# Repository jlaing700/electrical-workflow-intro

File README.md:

Note: There are two methods in which you can publish your work through Github. 
1. Using Git Bash CD (Command Prompts)
2. Using GitHub Desktop app and/or GitHub website.

Pick whichever you're comfortable with. If you're not a coding person, I recommend using method 2. 

Make sure you have created a GitHub account before you start and have it shared with one of the electrical to be added to Mechatronics GitHub organization. 

# 1. GitHub-Work-Flow-Intro-Project using Git Bash
Add a .txt file telling club members about you and what your goals are for Fall 2022 semester

## How to Contribute to the Repository
Here is a brief explanation on how to contribute to git and github

#### Git vs. Github
Git is a repository version control that is local to your computer only. This means only the user of the local computer has access to these files. It keeps track of any changes that are commited to it so that each iteration of a repo can be accessed. Be sure to update this each time you finish your work session for the day as it will act as a backup storage. Git is important for version control but also because this is where github will be pulling the files from whenever a "push" occurs. **You will need to install git onto your computer**

https://git-scm.com/downloads

Github is a cloud based repository viewer that allows a repository to be accessed via webapp. Github will act as a central location for all our individual tasks and develepments to be accessed from any computer connected to the internet. Changes should be comitted to Git first and then pushed to Github so anybody can access pull the changes to the repository.

#### Cloning
To make the initial link of a github repository onto your git, you must clone it. Here are the steps to doing so

1. Open git bash or linux terminal in the working directory of where you wish to store the repository files on your computer. This is can be done by right-clicking inside the folder you save the files and selecting "Git Bash Here"

2. Use the clone command to clone the github repository onto your git. It will automatically create a folder with the name of the repository with all of its contents
```
git clone https://github.com/Mechatronics-SDSU/electrical-workflow-intro.git
```

#### Branching
Every repository, in our case **GitHub_Work_Flow_Intro_Project**, has a **main** branch where the most up-to-date ready to ship version is held. This is to ensure there is always a deployable version at any point in the development and maintenance cycle. When new features or additions are being developed, typically a new branch is created with the name of that feature. This allows for a new location that new code, PCB designs, and updates can be saved without affecting the **main** branch. In our case, there currently exists a branch for each seperate piece to the project. Once one of the features/branches has been thoroughly tested and is stable, that branch is merged into the **main** branch. What this will do is copy all files from the initial development branch and merge them into the **main** branch so it becomes the most up-to-date version with these new features.

Here is an example of how to create a new branch off of main. Please use the following naming format for the branch **[Your_Full_Name]_[Description of Branch]**, for the intro project please use **dev** as your branch description.

#### Creating a New Branch Example

Create a new branch off of **electrical-workflow-intro** called "Tristan_dev"

```
git checkout -b Tristan_dev main
```

#### Git Workflow

Here is a step by step explanation of how a typical worksession goes

1. Open git bash or linux terminal in the working directory of where you store the repository files on your computer. This is can be done by right-clicking inside the folder you save the files and selecting "Git Bash Here"

2. Pull any and all changes from the github repository **main** to be saved into your local git. Note you must enter the exact branches you wish to update your local version of to the github version. See step 3 on how to change current branch. 
```
git pull
```

3. Enter the exact branch you wish to do development in. Important to do this step as failure to do so may result in conflicts
```
git checkout [Name_of_Branch]
```

4. Start developing as you normally do until you are all finished

5. Add the specific files that were worked on
```
git add file.txt

or

git add -A
```

6. Commit the changes to the added files to the local git with a message of what was changed. It is important to add a message as the commit will open up VIM expecting you to write a message in. **To avoid this issue, be sure to write the message in the initial commit command**
```
git commit -m "Programmed the Arduino to blink an LED every 5 seconds"
```

7. Push these commits in your local git to the github so everyone can pull these changes to their local computers
```
git push origin [Name_of_Branch]
```

8. A pop window will appear prompting for you github login information. Enter you username into the first window and click submit, then enter you password into the second window and click submit.
-----------------------------------------------------------------------------------------------------------------------------------------------------------------------

# 2. GitHub-Work-Flow-Intro-Project Using GitHub Desktop
**Download and install GitHub Desktop App on your computer: https://desktop.github.com/**

**Make sure you're using the same account for both GitHub website and GitHub Desktop App.**

## There are a total of 3 steps on how to contribute to the repository:
1. Cloning
2. Branching
3. Pushing 
-----------------------------------------------------------------------------------------------------------------------------------------------------------------------
- Cloning and Branching are usually only done once. 

- To contribute to a Repository, you must clone it on your local computer. 

- Branching is a cloned version of a repository in order to push any work you've done pertaining the intruction of that Repository. 

- Pushing is uploading your files/work you've done to GitHub where anyone who has access to the Repository can see your files that you pushed. 

In these steps below, l'll walk you through how to contribute to a Repository using GitHub Desktop app and GitHub website. 

-----------------------------------------------------------------------------------------------------------------------------------------------------------------------

1. Create a text file on your desktop. Within the text file, tell us about you and what your goals are for Fall 2022 semester. For more brownie points, add in any particular interests that you would like to work with/learn more about in our electrical team. 

Now that your text file is ready to be shared on GitHub, we'll first have to add yourself to this repository to create a branch. 

A branch is a cloned version of a repository. In this case, we'll create a branch named after your name (e.g: Fadi_dev) of this repository.

Within this new branch that you will create, you will be able to add in any files that pertains to the repository instructions. 

(More information about GitHub, Branching, and Cloning can be found in the sections above in method 1)

2. To add yourself to the repository, navigate and press the main branch on the GitHub website. 
Navigate to "Code" --> "Open with GitHub Desktop". From there, GitHub desktop will clone the repository of main branch and add it to your local computer. After the clone has finished, you will now be able to create your own personal branch. 
3. On the GitHub Desktop app, navigate to "Current branch" and press "New branch". Create a branch named after your name (e.g: Fadi_dev). 
You can also do this on the main GitHub website to create a branch. 

Congratualtions, you now have your own personal branch of this repository. 

4. After you have made your branch, navigate to it and press, you will notice that the README.md instructions are cloned to your branch. 
Next step is to add your .txt file that you have already made on your desktop. All thats left to do is to upload your .txt file to github **while** you're in your created branch (this is important). 

Once you've uploaded your text file, you should be able to see what you've wrote down on GitHub. Anyone who has access to this repository is also able to see it. 

-----------------------------------------------------------------------------------------------------------------------------------------------------------------------
**If you have any questions, reach out to Ken or sudo apt install better grades on Discord**

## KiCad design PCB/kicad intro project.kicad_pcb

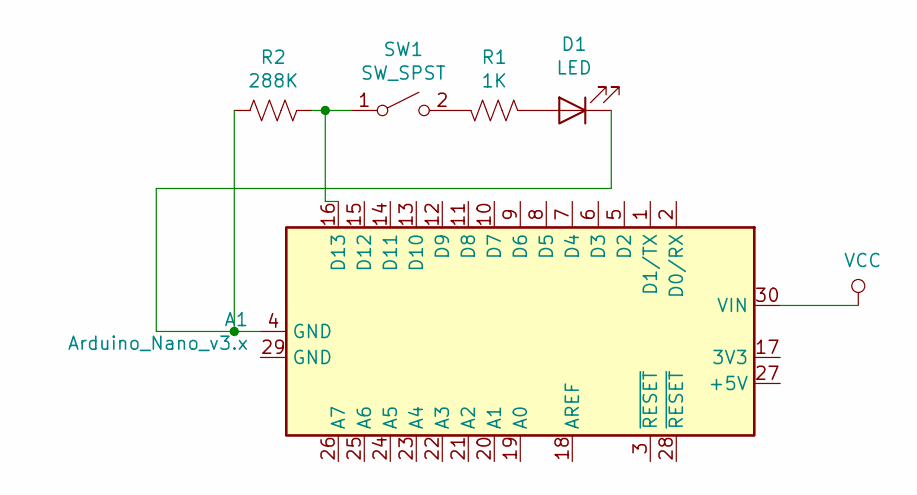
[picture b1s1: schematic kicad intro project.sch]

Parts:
A1: Arduino_Nano_v3.x; Arduino_Nano
D1: LED; LED_D3.0mm_Horizontal_O3.81mm_Z10.0mm
R1: 1K; R_Axial_DIN0204_L3.6mm_D1.6mm_P1.90mm_Vertical
R2: 288K; R_Axial_DIN0204_L3.6mm_D1.6mm_P1.90mm_Vertical
SW1: SW_SPST; TerminalBlock_RND_205-00012_1x02_P5.00mm_Horizontal

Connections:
unnamed: A1.4 (GND), D1.1 (K), R2.1
unnamed: A1.16 (D13), R2.2, SW1.1 (A)
unnamed: D1.2 (A), R1.2
unnamed: R1.1, SW1.2 (B)
VCC: A1.30 (VIN)

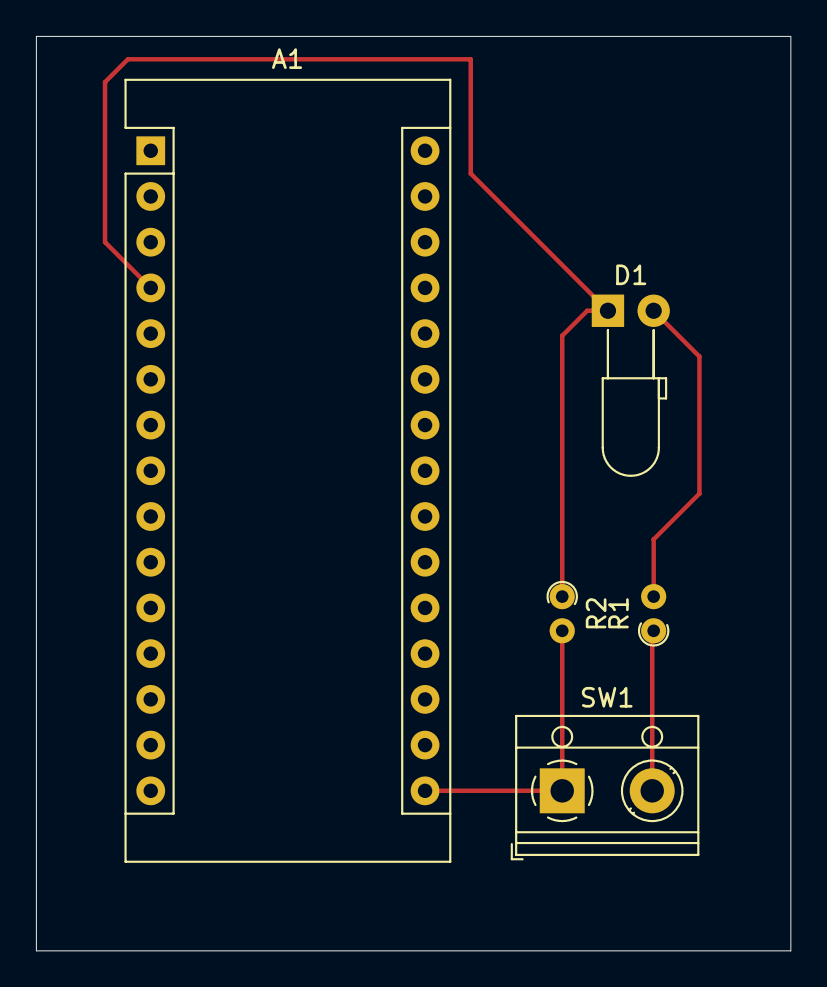
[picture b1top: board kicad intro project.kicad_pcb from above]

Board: 2 copper layers, 41.9 x 50.8 mm, 5 parts (0 on the bottom side), 4 nets.

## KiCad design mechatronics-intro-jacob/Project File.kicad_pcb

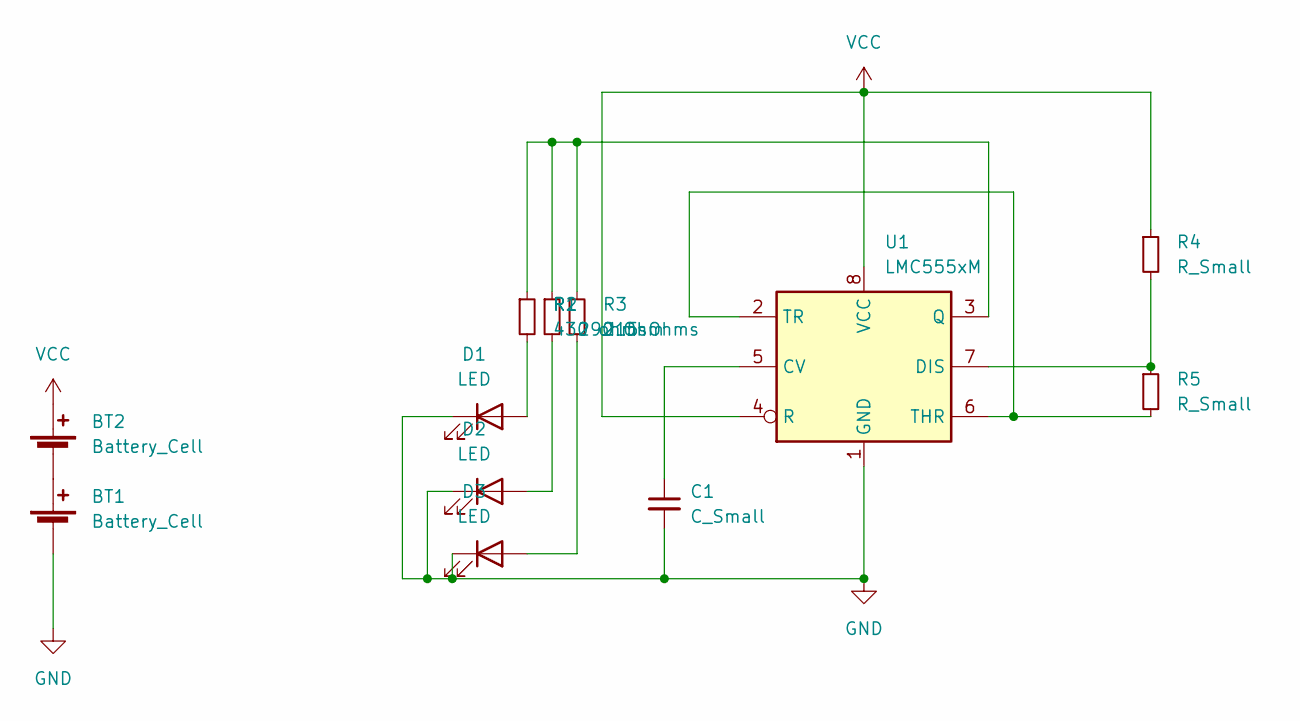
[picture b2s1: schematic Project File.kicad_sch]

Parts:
BT1, BT2: Battery_Cell; BatteryHolder_LINX_BAT-HLD-012-SMT
C1: C_Small; C_0805_2012Metric_Pad1.18x1.45mm_HandSolder
D1, D2, D3: LED; LED_0805_2012Metric_Pad1.15x1.40mm_HandSolder
R1: 430 ohms; R_0805_2012Metric_Pad1.20x1.40mm_HandSolder
R2: 290 Ohm; R_0805_2012Metric_Pad1.20x1.40mm_HandSolder
R3: 215 Ohms; R_0805_2012Metric_Pad1.20x1.40mm_HandSolder
R4, R5: R_Small; R_0805_2012Metric_Pad1.20x1.40mm_HandSolder
U1: LMC555xM; SOIC-8-1EP_3.9x4.9mm_P1.27mm_EP2.62x3.51mm

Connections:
GND: BT1.2 (-), C1.2, D1.1 (K), D2.1 (K), D3.1 (K), U1.1 (GND)
unnamed: BT1.1 (+), BT2.2 (-)
unnamed: C1.1, U1.5 (CV)
unnamed: D1.2 (A), R1.2
unnamed: D2.2 (A), R2.2
unnamed: D3.2 (A), R3.2
unnamed: R1.1, R2.1, R3.1, U1.3 (Q)
unnamed 7: R4.2, R5.1, U1.7 (DIS); also elsewhere on the board
unnamed 8: R5.2, U1.2 (TR), U1.6 (THR); also elsewhere on the board
VCC: BT2.1 (+), R4.1, U1.4 (R), U1.8 (VCC)

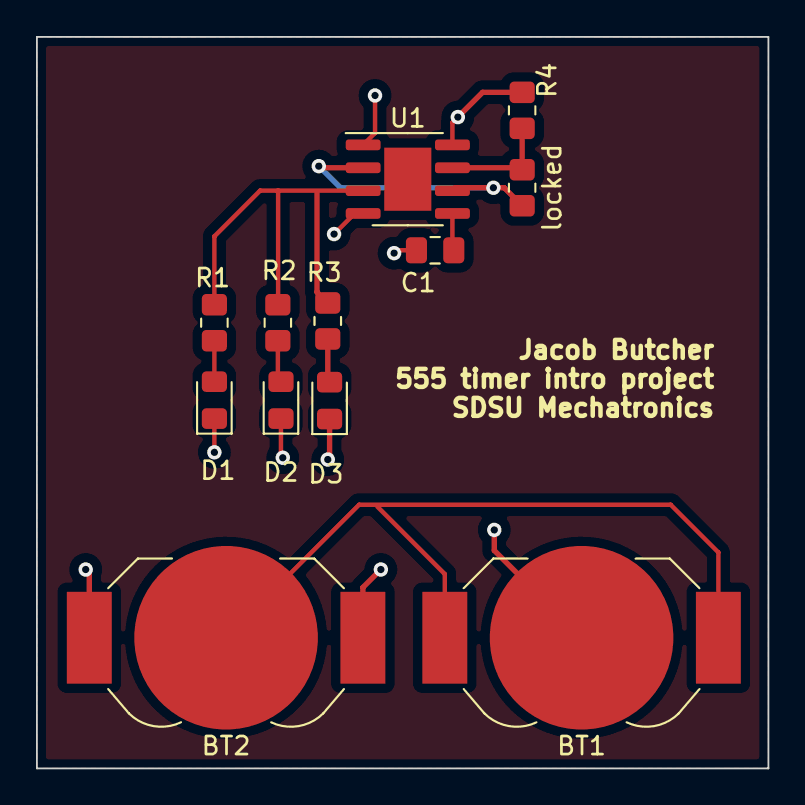
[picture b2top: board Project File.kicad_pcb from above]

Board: 4 copper layers, 40.6 x 40.6 mm, 12 parts (0 on the bottom side), 10 nets.

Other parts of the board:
locked: R_Small; R_0805_2012Metric_Pad1.20x1.40mm_HandSolder

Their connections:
unnamed 7: locked.1; also elsewhere on the board
unnamed 8: locked.2; also elsewhere on the board

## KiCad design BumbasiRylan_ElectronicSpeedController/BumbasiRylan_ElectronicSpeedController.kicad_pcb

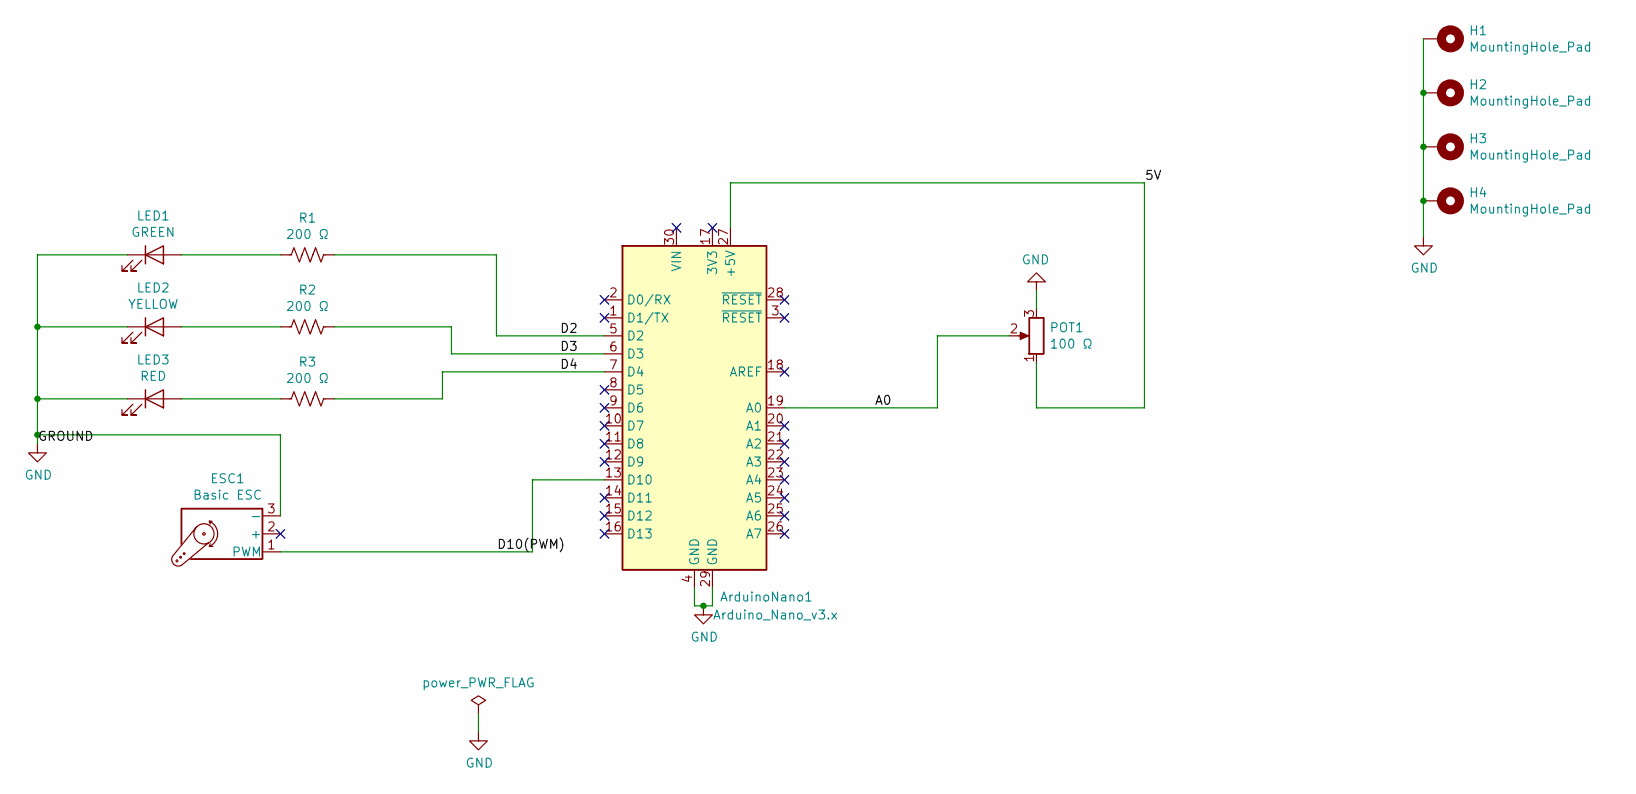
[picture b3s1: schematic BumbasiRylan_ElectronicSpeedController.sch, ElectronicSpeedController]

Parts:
ArduinoNano1: Arduino_Nano_v3.x; Arduino_Nano
ESC1: Basic ESC; PinHeader_1x03_P2.54mm_Vertical
H1, H2, H3, H4: MountingHole_Pad; MountingHole_3mm_Pad_Via
LED1: GREEN; LED_D5.0mm
LED2: YELLOW; LED_D5.0mm
LED3: RED; LED_D5.0mm
POT1: 100 Ω; Potentiometer_Alps_RK09Y11_Single_Horizontal
R1, R2, R3: 200 Ω; R_Axial_DIN0207_L6.3mm_D2.5mm_P10.16mm_Horizontal

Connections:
/5V: ArduinoNano1.27 (+5V), POT1.1
/A0: ArduinoNano1.19 (A0), POT1.2
/D2: ArduinoNano1.5 (D2), R1.1
/D3: ArduinoNano1.6 (D3), R2.1
/D4: ArduinoNano1.7 (D4), R3.1
/D10(PWM): ArduinoNano1.13 (D10), ESC1.1 (PWM)
GND: ArduinoNano1.4 (GND), ArduinoNano1.29 (GND), ESC1.3 (-), H1.1, H2.1, H3.1, H4.1, LED1.1 (K), LED2.1 (K), LED3.1 (K), POT1.3
unnamed: LED1.2 (A), R1.2
unnamed: LED2.2 (A), R2.2
unnamed: LED3.2 (A), R3.2

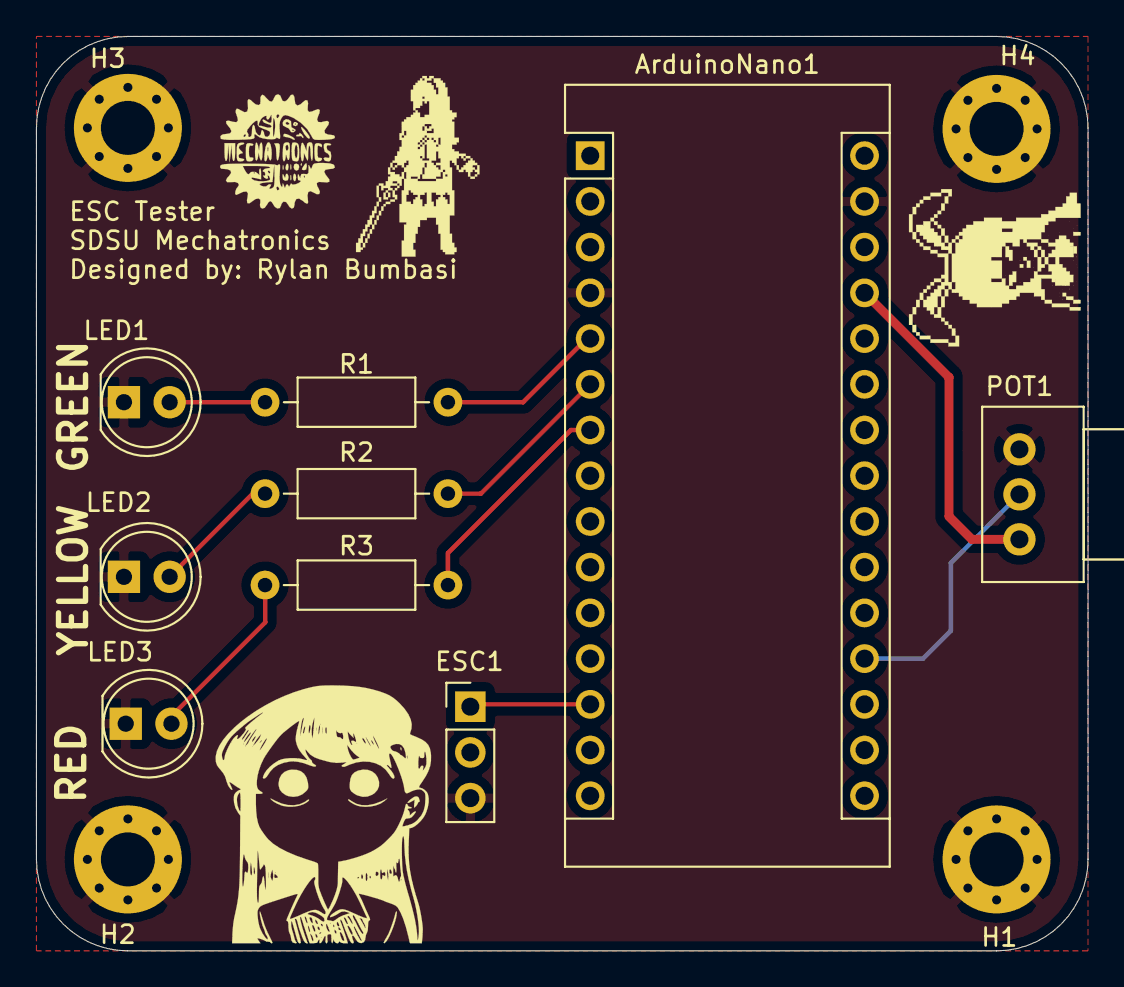
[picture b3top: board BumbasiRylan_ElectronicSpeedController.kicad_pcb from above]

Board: 2 copper layers, 58.4 x 50.8 mm, 13 parts (0 on the bottom side), 10 nets.

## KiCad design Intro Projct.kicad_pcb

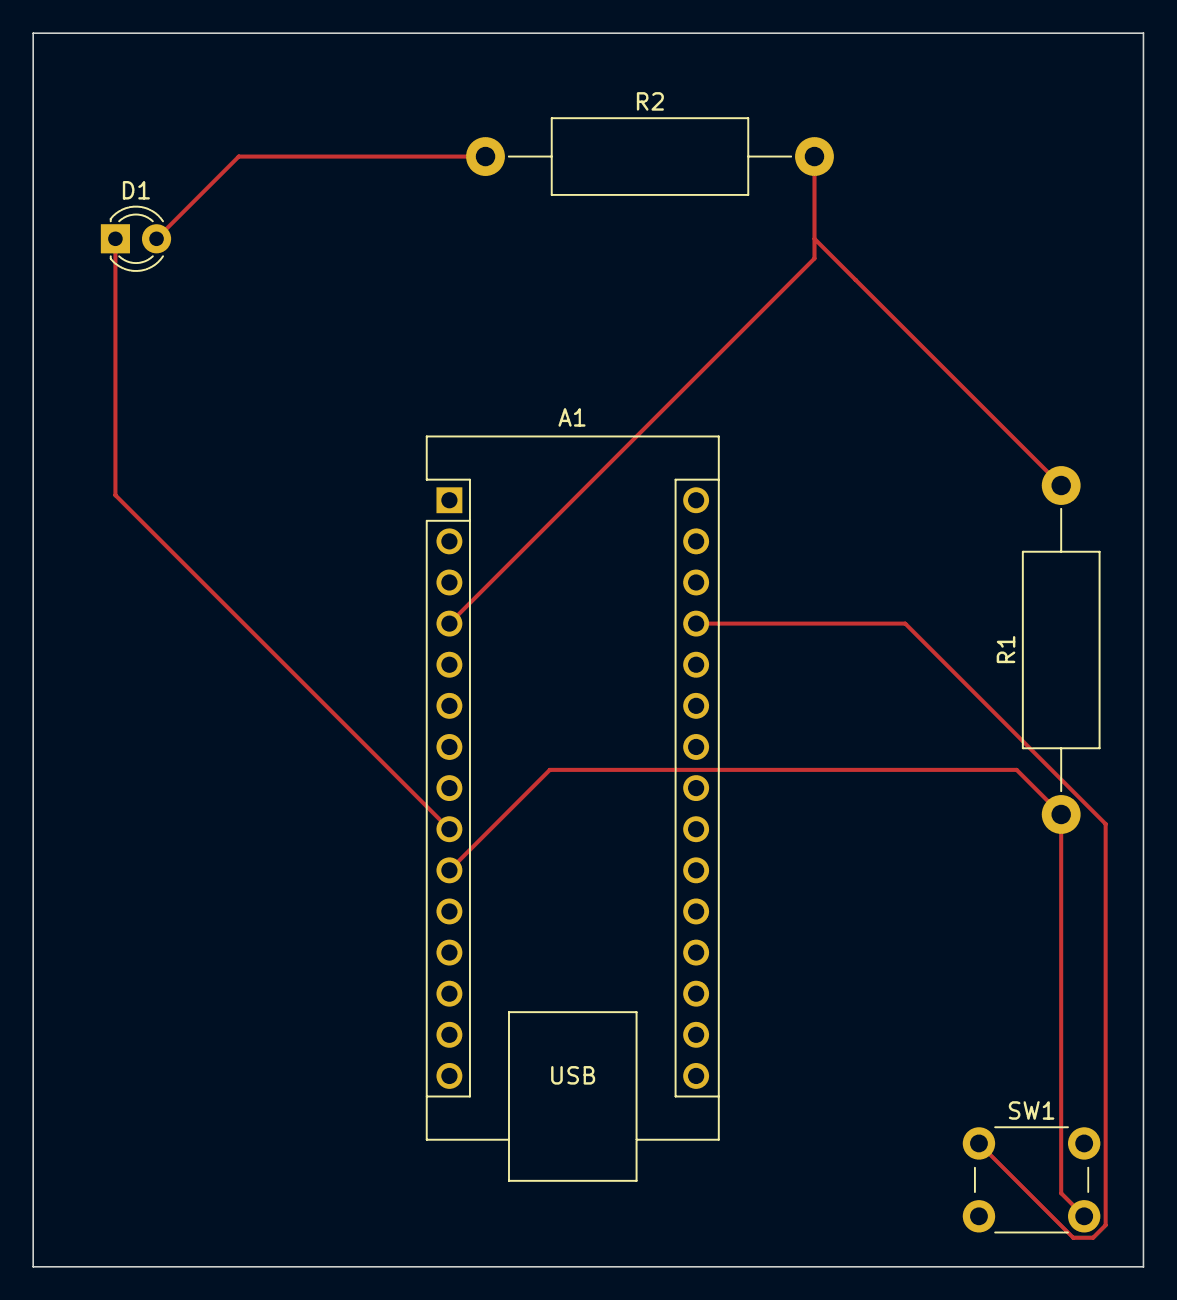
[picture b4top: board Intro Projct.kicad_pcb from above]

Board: 2 copper layers, 68.6 x 76.2 mm, 5 parts (0 on the bottom side), 5 nets.

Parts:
A1: Arduino_Nano_v2.x; Arduino_Nano
D1: LED; LED_D3.0mm_Clear
R1: 10k Ohms; R_Axial_DIN0414_L11.9mm_D4.5mm_P20.32mm_Horizontal
R2: 330 Ohms; R_Axial_DIN0414_L11.9mm_D4.5mm_P20.32mm_Horizontal
SW1: SW_Push; SW_PUSH_6mm_H13mm

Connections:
unnamed: A1.27 (+5V), SW1.1
unnamed: A1.9 (D6), D1.1 (K)
unnamed: A1.10 (D7), R1.1, SW1.2
unnamed: A1.4 (GND), R1.2, R2.2
unnamed: D1.2 (A), R2.1

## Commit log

2021-08-09 adding .txt for intro project
2021-08-16 Uploaded an introduction txt file
2021-08-28 Added Kyle_intro.txt
2021-08-28 Eli intro
    Hello
2021-08-28 Added finished Frequency Detection Intro Task
2021-08-29 Rename Eli Intro to Eli-Intro.txt
2021-09-06 Added test FIR filter code
2021-09-09 Added timer interrupts and buffer shifting
2021-09-11 Create doc
2021-09-11 Rename CANtest-recieve.ino to CANtest1/CANtest-recieve.ino
2021-09-11 Rename CANtest-send.ino to CANtest1/CANtest-send.ino
2021-09-11 Update doc
2021-09-20 Pushing KiCad intro project files
2021-09-20 First revision
2021-09-20 Pushed Gerber Files
2021-10-01 Increased 5v Trace Width
2021-10-01 Updated units for gerbers
2021-10-01 Added Drill Map Files
2022-01-15 First intro text
2022-01-19 Uploading Intro Project
2022-01-24 Uploading pcb.zip
2022-01-29 pushed cache to rylan
2022-01-29 Added a .txt file
2022-02-18 this is a test
2022-02-20 testing programm w git rn
2022-02-21 removed intro project commit error
2022-02-21 Revert "Update README.md"
    This reverts commit 89d8f443f51321455755a28c11ca8c340bbefac3.
    reverted old main
2022-02-21 revert debug
2022-03-22 Create Lorance_dev
2022-08-31 project complete
2022-09-04 Create introTest
2022-09-04 intro text file
2022-09-04 Added Goals.txt as per instruction
2022-09-07 Poggers
2022-09-07 Added actual readme relevant to the program
2022-09-10 Create LedBrightnessControlWithPB.ino
    Code for intro project. Pin numbers will have to be verified since the actual PCB will use arduino NANO but this code was made for UNO
2022-09-10 Uploaded hw
    330 HW
2022-09-10 added goals to intro
2022-09-16 Create Mechatronics_Matthew_Steel.txt
    Added about me
2022-09-16 Create Matthew-Steel-Electrical-Intro-Project.ino
    Intro project code
2022-09-17 Code + intro
2022-09-18 Dim LED Code
2022-09-18 Rename Button_LED_Dim_Peter_Kottis.txt.ino to Button_LED_Dim_Peter_Kottis.ino
2022-09-21 Servo Project Code
    This was a project that had the servo default to 90 degrees or go either right or left
2022-10-03 Intro Project Arduino Code
    This is the code for the intro project in the Arduino end.
2022-10-06 Create electricalstuff.ino
    Code
2022-10-06 text is up
2022-10-07 lets go git push
2022-10-08 clearing
2023-01-24 updated contact information
2023-02-22 Intro Project
2023-02-25 Project Files
    Code and gbr files for the Intro Project
2023-02-27 Here is everything
